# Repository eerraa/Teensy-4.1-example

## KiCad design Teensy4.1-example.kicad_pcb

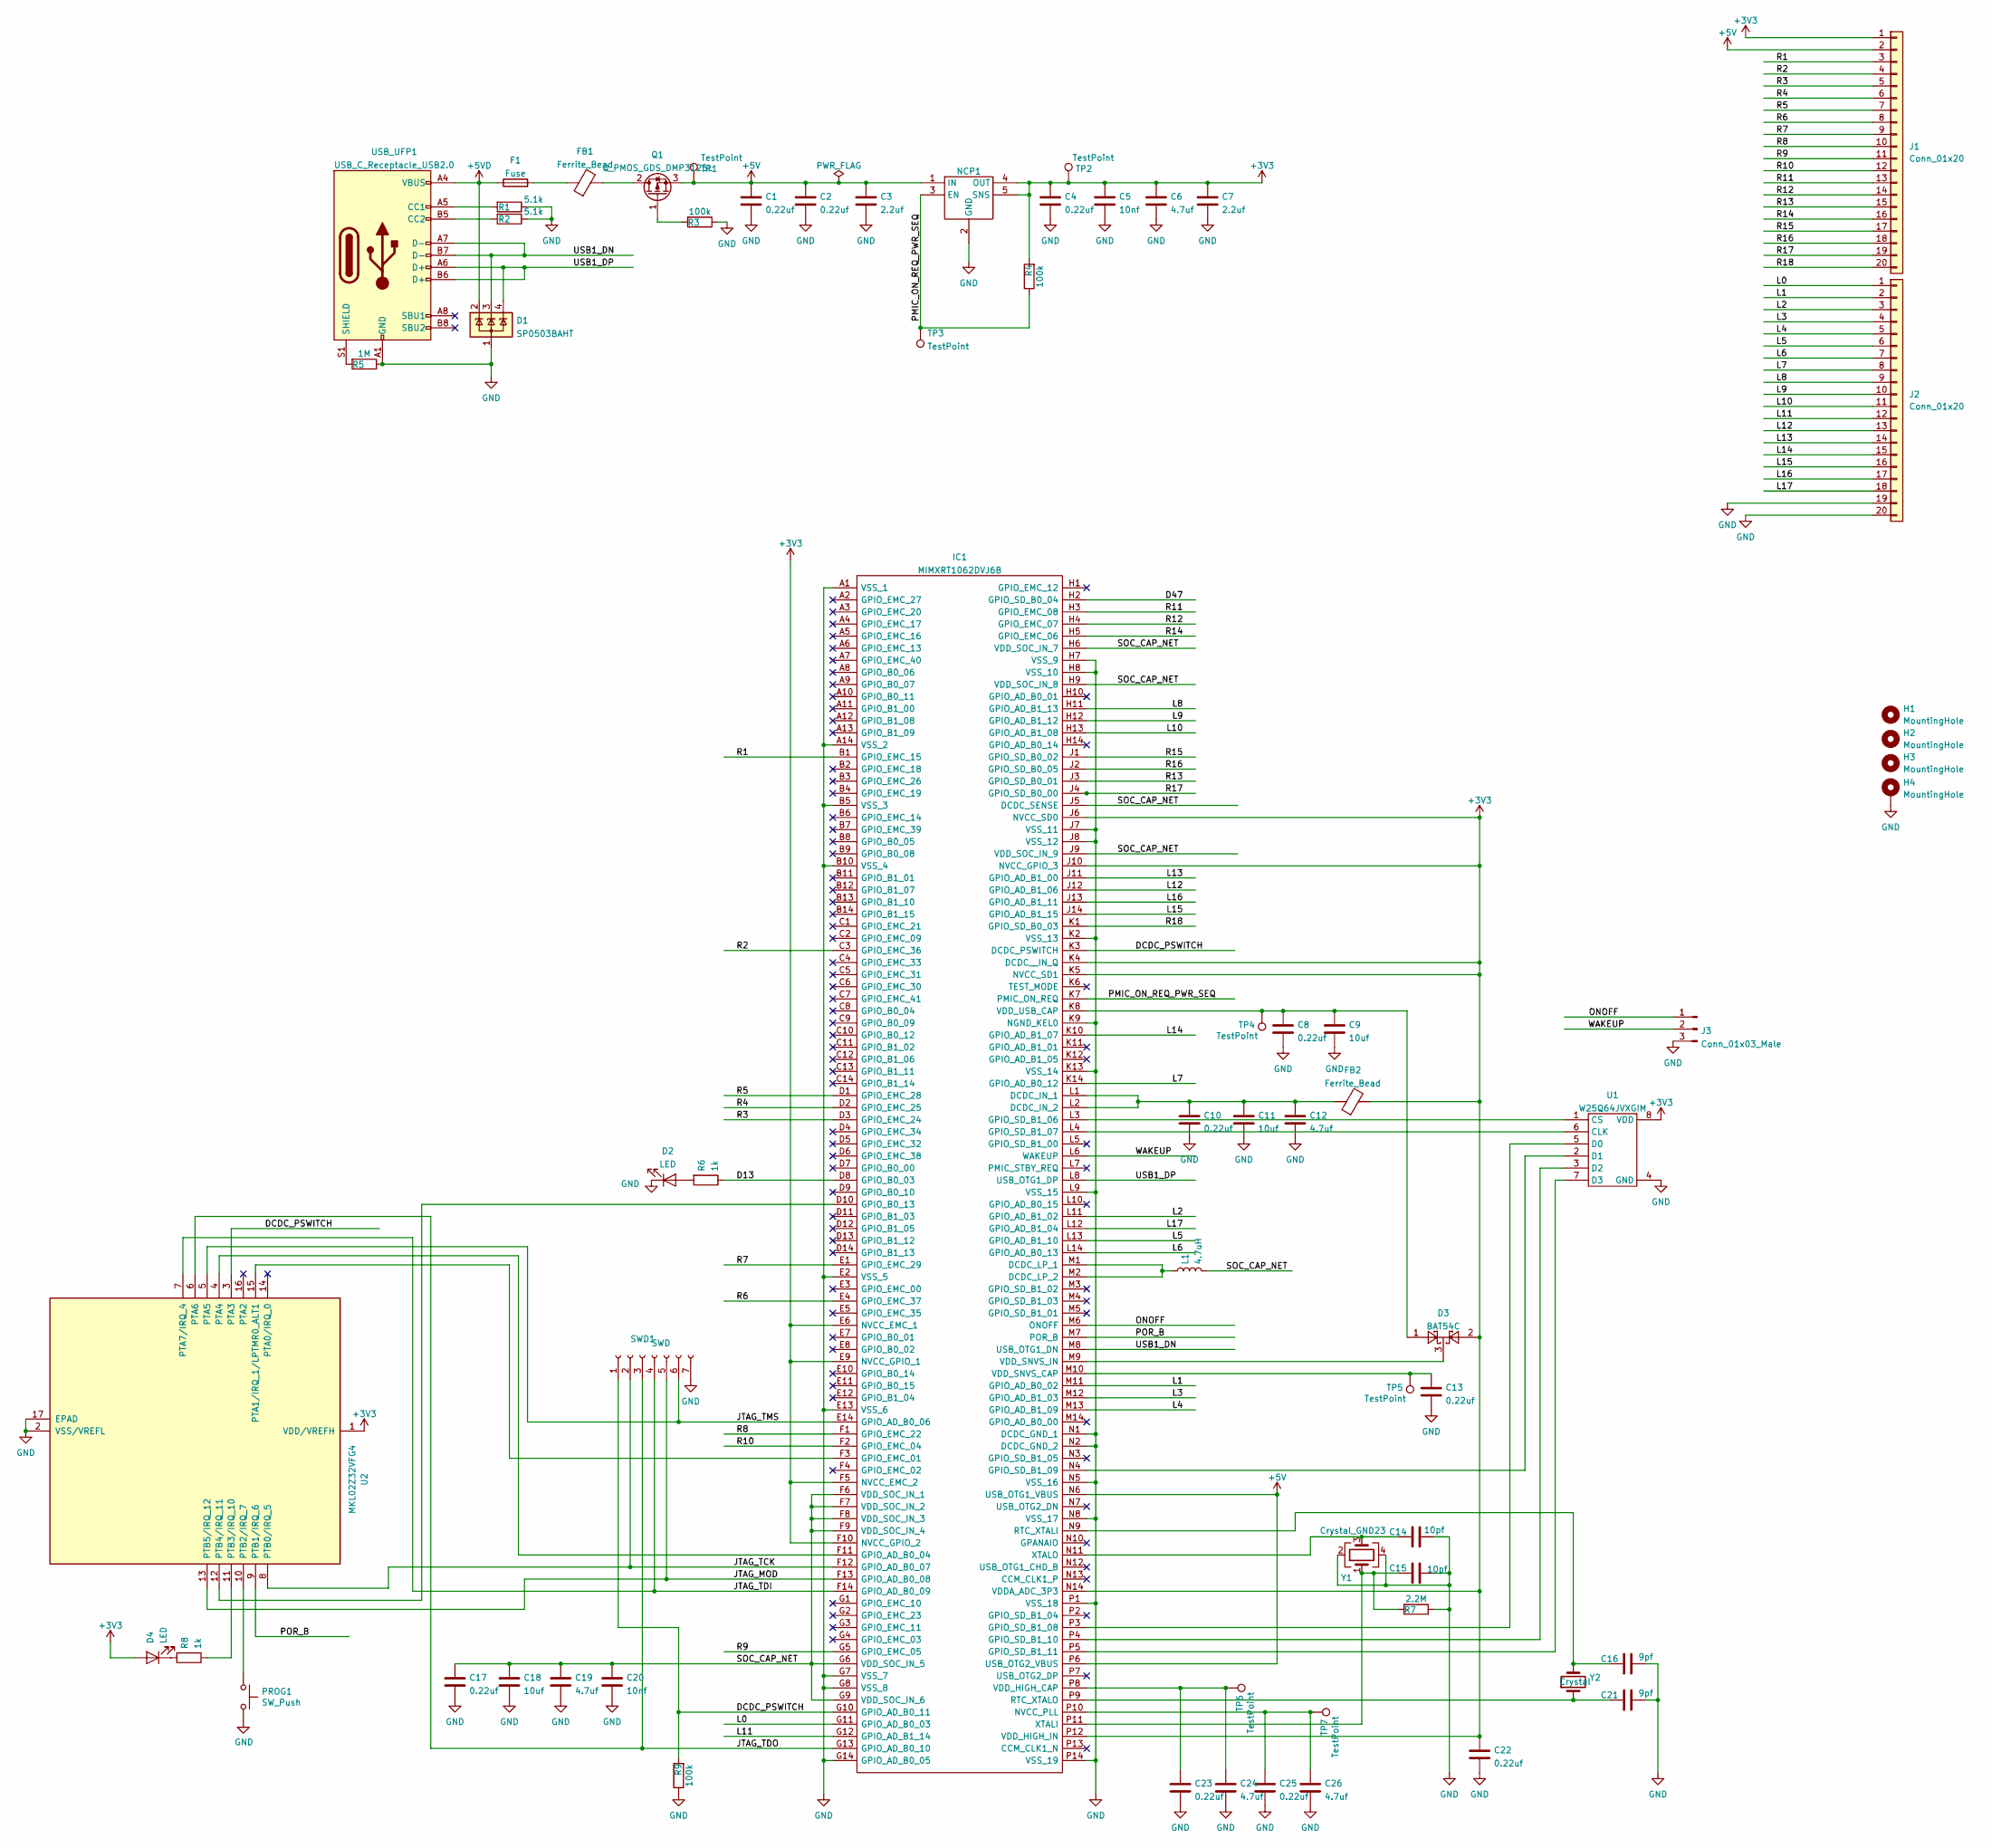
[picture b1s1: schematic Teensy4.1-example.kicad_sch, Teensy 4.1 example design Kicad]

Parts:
C1, C2, C4, C8, C10, C13, C17, C22, C23, C25: 0.22uf; C_0603_1608Metric; MPN CC0603KRX7R6BB224
C3, C7: 2.2uf; C_0603_1608Metric; MPN CL10B225KP8NNNC
C5, C20: 10nf; C_0603_1608Metric; MPN 0603B103K160CT
C6, C12, C19, C24, C26: 4.7uf; C_0603_1608Metric; MPN CL10B475KQ8NQNC
C9, C11, C18: 10uf; C_0805_2012Metric; MPN GRM21BR71A106KA73K
C14, C15: 10pf; C_0603_1608Metric; MPN CC0603KRX7R6BB224
C16, C21: 9pf; C_0603_1608Metric; MPN GRM1885C1H9R0DA01D
D1: SP0503BAHT; SOT-143
D2, D4: LED; LED_0402_1005Metric
D3: BAT54C; SOT-23
F1: Fuse; R_0805_2012Metric; MPN 0ZCK0050FF2E
FB1, FB2: Ferrite_Bead; R_0805_2012Metric; MPN FBMH2012HM121-T‎
H1, H2, H3, H4: MountingHole; MountingHole_2.7mm_M2.5_DIN965_Pad_TopBottom
IC1: MIMXRT1062DVJ6B; BGA196C80P14X14_1200X1200X152; Mouser Part Number 771-MIMXRT1062DVJ6B
J1, J2: Conn_01x20; Hirose_FH12-20S-0.5SH_1x20-1MP_P0.50mm_Horizontal
J3: Conn_01x03_Male; PinHeader_1x03_P2.54mm_Vertical
L1: 4.7uH; C_0805_2012Metric; MPN LQM21PN4R7MGRD
NCP1: OnSemi NCP692, fixed version; DFN-6-1EP_3x3mm_P0.95mm_EP1.7x2.6mm; MPN NCP692MN33T2G
PROG1: SW_Push; KMR241GLFS; MPN KMR241GLFS
Q1: Q_PMOS_GDS_DMP3125L; SOT-23
R1, R2: 5.1k; R_0603_1608Metric; MPN RC0603FR-075K1L
R3, R4, R9: 100k; R_0603_1608Metric
R5: 1M; R_0603_1608Metric
R6, R8: 1k; R_0402_1005Metric
R7: 2.2M; R_0603_1608Metric
SWD1: SWD; PinHeader_1x07_P1.27mm_Vertical
TP1, TP2, TP3, TP4, TP5, TP6, TP7: TestPoint; TestPoint_Pad_D1.0mm
U1: W25Q64JVXGIM; XSON8_4x4mm
U2: MKL02Z32VFG4; QFN-16-1EP_3x3mm_P0.5mm_EP1.8x1.8mm; MPN Custom firmware part
USB_UFP1: USB_C_Receptacle_USB2.0; USB_C_Receptacle_Hroparts_TYPE-C-31-M-12
Y1: Crystal_GND23; Crystal_SMD_Abracon_ABM3B-4Pin_5.0x3.2mm
Y2: Crystal; Crystal_SMD_2012-2Pin_2.0x1.2mm; MPN ABS06-32.768KHZ-9-1-T

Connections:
+3V3: C4.1, C5.1, C6.1, C7.1, C22.1, D3.2, D4.2 (A), FB2.2, IC1.E6 (NVCC_EMC_1), IC1.E9 (NVCC_GPIO_1), IC1.F5 (NVCC_EMC_2), IC1.F10 (NVCC_GPIO_2), IC1.J6 (NVCC_SD0), IC1.J10 (NVCC_GPIO_3), IC1.K4 (DCDC__IN_Q), IC1.K5 (NVCC_SD1), IC1.N14 (VDDA_ADC_3P3), IC1.P12 (VDD_HIGH_IN), J1.1, NCP1.4 (OUT), NCP1.5 (SNS), R4.2, TP2.1, U1.8 (VDD), U2.1 (VDD/VREFH)
+5V: C1.1, C2.1, C3.1, IC1.N6 (USB_OTG1_VBUS), IC1.P6 (USB_OTG2_VBUS), J1.2, NCP1.1 (IN), NCP1.6 (IN), Q1.3 (S), TP1.1
+5VD: D1.2 (K), F1.1, USB_UFP1.A4 (VBUS), USB_UFP1.A9 (VBUS), USB_UFP1.B4 (VBUS), USB_UFP1.B9 (VBUS)
/D13: IC1.D8 (GPIO_B0_03), R6.1
/D47: IC1.H2 (GPIO_SD_B0_04)
/DCDC_PSWITCH: IC1.G10 (GPIO_AD_B0_11), IC1.K3 (DCDC_PSWITCH), R9.2, SWD1.1, U2.3 (PTA3)
/JTAG_MOD: IC1.F13 (GPIO_AD_B0_08), SWD1.5, U2.13 (PTB5/IRQ_12)
/JTAG_TCK: IC1.F12 (GPIO_AD_B0_07), SWD1.2, U2.8 (PTB0/IRQ_5)
/JTAG_TDI: IC1.F14 (GPIO_AD_B0_09), SWD1.4, U2.7 (PTA7/IRQ_4)
/JTAG_TDO: IC1.G13 (GPIO_AD_B0_10), SWD1.3, U2.6 (PTA6)
/JTAG_TMS: IC1.E14 (GPIO_AD_B0_06), SWD1.6, U2.5 (PTA5)
/L0: IC1.G11 (GPIO_AD_B0_03), J2.1
/L1: IC1.M11 (GPIO_AD_B0_02), J2.2
/L2: IC1.L11 (GPIO_AD_B1_02), J2.3
/L3: IC1.M12 (GPIO_AD_B1_03), J2.4
/L4: IC1.M13 (GPIO_AD_B1_09), J2.5
/L5: IC1.L13 (GPIO_AD_B1_10), J2.6
/L6: IC1.L14 (GPIO_AD_B0_13), J2.7
/L7: IC1.K14 (GPIO_AD_B0_12), J2.8
/L8: IC1.H11 (GPIO_AD_B1_13), J2.9
/L9: IC1.H12 (GPIO_AD_B1_12), J2.10
/L10: IC1.H13 (GPIO_AD_B1_08), J2.11
/L11: IC1.G12 (GPIO_AD_B1_14), J2.12
/L12: IC1.J12 (GPIO_AD_B1_06), J2.13
/L13: IC1.J11 (GPIO_AD_B1_00), J2.14
/L14: IC1.K10 (GPIO_AD_B1_07), J2.15
/L15: IC1.J14 (GPIO_AD_B1_15), J2.16
/L16: IC1.J13 (GPIO_AD_B1_11), J2.17
/L17: IC1.L12 (GPIO_AD_B1_04), J2.18
/ONOFF: IC1.M6 (ONOFF), J3.1
/PMIC_ON_REQ_PWR_SEQ: IC1.K7 (PMIC_ON_REQ), NCP1.3 (EN), R4.1, TP3.1
/POR_B: IC1.M7 (POR_B), U2.9 (PTB1/IRQ_6)
/R1: IC1.B1 (GPIO_EMC_15), J1.3
/R2: IC1.C3 (GPIO_EMC_36), J1.4
/R3: IC1.D3 (GPIO_EMC_24), J1.5
/R4: IC1.D2 (GPIO_EMC_25), J1.6
/R5: IC1.D1 (GPIO_EMC_28), J1.7
/R6: IC1.E4 (GPIO_EMC_37), J1.8
/R7: IC1.E1 (GPIO_EMC_29), J1.9
/R8: IC1.F1 (GPIO_EMC_22), J1.10
/R9: IC1.G5 (GPIO_EMC_05), J1.11
/R10: IC1.F2 (GPIO_EMC_04), J1.12
/R11: IC1.H3 (GPIO_EMC_08), J1.13
/R12: IC1.H4 (GPIO_EMC_07), J1.14
/R13: IC1.J3 (GPIO_SD_B0_01), J1.15
/R14: IC1.H5 (GPIO_EMC_06), J1.16
/R15: IC1.J1 (GPIO_SD_B0_02), J1.17
/R16: IC1.J2 (GPIO_SD_B0_05), J1.18
/R17: IC1.J4 (GPIO_SD_B0_00), J1.19
/R18: IC1.K1 (GPIO_SD_B0_03), J1.20
/SOC_CAP_NET: C17.1, C18.1, C19.1, C20.1, IC1.F6 (VDD_SOC_IN_1), IC1.F7 (VDD_SOC_IN_2), IC1.F8 (VDD_SOC_IN_3), IC1.F9 (VDD_SOC_IN_4), IC1.G6 (VDD_SOC_IN_5), IC1.G9 (VDD_SOC_IN_6), IC1.H6 (VDD_SOC_IN_7), IC1.H9 (VDD_SOC_IN_8), IC1.J5 (DCDC_SENSE), IC1.J9 (VDD_SOC_IN_9), L1.2
/USB1_DN: D1.3 (K), IC1.M8 (USB_OTG1_DN), USB_UFP1.A7 (D-), USB_UFP1.B7 (D-)
/USB1_DP: D1.4 (K), IC1.L8 (USB_OTG1_DP), USB_UFP1.A6 (D+), USB_UFP1.B6 (D+)
/WAKEUP: IC1.L6 (WAKEUP), J3.2
GND: C1.2, C2.2, C3.2, C4.2, C5.2, C6.2, C7.2, C8.2, C9.2, C10.2, C11.2, C12.2, C13.2, C14.2, C15.2, C16.2, C17.2, C18.2, C19.2, C20.2, C21.2, C22.2, C23.2, C24.2, C25.2, C26.2, D1.1 (A), D2.1 (K), H4.1, IC1.A1 (VSS_1), IC1.A14 (VSS_2), IC1.B5 (VSS_3), IC1.B10 (VSS_4), IC1.E2 (VSS_5), IC1.E13 (VSS_6), IC1.G7 (VSS_7), IC1.G8 (VSS_8), IC1.G14 (GPIO_AD_B0_05), IC1.H7 (VSS_9), IC1.H8 (VSS_10), IC1.J7 (VSS_11), IC1.J8 (VSS_12), IC1.K2 (VSS_13), IC1.K9 (NGND_KEL0), IC1.K13 (VSS_14), IC1.L9 (VSS_15), IC1.N1 (DCDC_GND_1), IC1.N2 (DCDC_GND_2), IC1.N5 (VSS_16), IC1.N8 (VSS_17), IC1.P1 (VSS_18), IC1.P14 (VSS_19), J2.19, J2.20, J3.3, NCP1.2 (GND), NCP1.7 (GND), PROG1.2, R1.1, R2.1, R3.1, R5.1, R7.1, R9.1, SWD1.7, U1.4 (GND), U2.2 (VSS/VREFL), U2.17 (EPAD), USB_UFP1.A1 (GND), USB_UFP1.A12 (GND), USB_UFP1.B1 (GND), USB_UFP1.B12 (GND), Y1.2, Y1.4
unnamed: D2.2 (A), R6.2
unnamed: D4.1 (K), R8.2
unnamed: F1.2, FB1.1
unnamed: C10.1, C11.1, C12.1, FB2.1, IC1.L1 (DCDC_IN_1), IC1.L2 (DCDC_IN_2)
unnamed: IC1.M1 (DCDC_LP_1), IC1.M2 (DCDC_LP_2), L1.1
unnamed: IC1.F11 (GPIO_AD_B0_04), U2.4 (PTA4)
unnamed: IC1.D10 (GPIO_B0_13), U2.12 (PTB4/IRQ_11)
unnamed: IC1.F3 (GPIO_EMC_01), U2.15 (PTA1/IRQ_1/LPTMR0_ALT1)
unnamed: IC1.L3 (GPIO_SD_B1_06), U1.1 (CS)
unnamed: IC1.L4 (GPIO_SD_B1_07), U1.6 (CLK)
unnamed: IC1.P3 (GPIO_SD_B1_08), U1.5 (D0)
unnamed: IC1.N4 (GPIO_SD_B1_09), U1.2 (D1)
unnamed: IC1.P4 (GPIO_SD_B1_10), U1.3 (D2)
unnamed: IC1.P5 (GPIO_SD_B1_11), U1.7 (D3)
unnamed: C25.1, C26.1, IC1.P10 (NVCC_PLL), TP7.1
unnamed: C16.1, IC1.N9 (RTC_XTALI), Y2.2
unnamed: C21.1, IC1.P9 (RTC_XTALO), Y2.1
unnamed: C23.1, C24.1, IC1.P8 (VDD_HIGH_CAP), TP6.1
unnamed: C13.1, IC1.M10 (VDD_SNVS_CAP), TP5.1
unnamed: D3.3, IC1.M9 (VDD_SNVS_IN)
unnamed: C8.1, C9.1, D3.1, IC1.K8 (VDD_USB_CAP), TP4.1
unnamed: C15.1, IC1.P11 (XTALI), R7.2, Y1.1
unnamed: C14.1, IC1.N11 (XTALO), Y1.3
unnamed: FB1.2, Q1.2 (D)
unnamed: Q1.1 (G), R3.2
unnamed: PROG1.1, U2.10 (PTB2/IRQ_7)
unnamed: R8.1, U2.11 (PTB3/IRQ_10)
unnamed: R1.2, USB_UFP1.A5 (CC1)
unnamed: R2.2, USB_UFP1.B5 (CC2)
unnamed: R5.2, USB_UFP1.S1 (SHIELD)

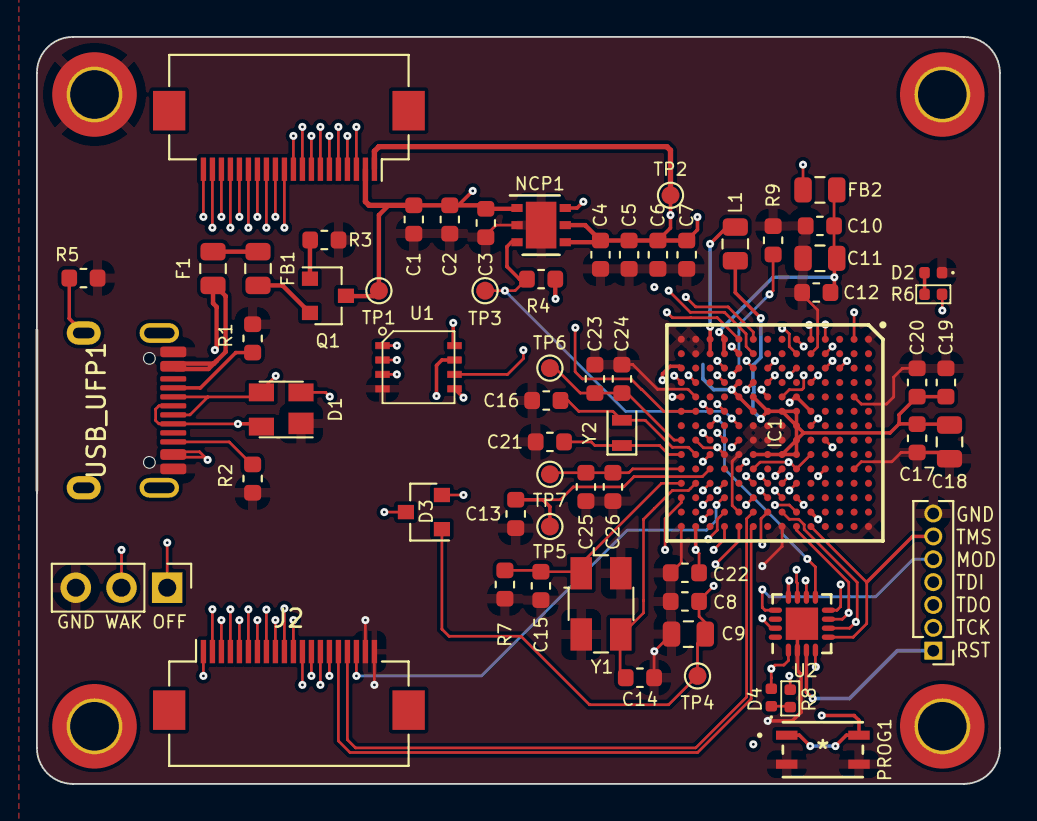
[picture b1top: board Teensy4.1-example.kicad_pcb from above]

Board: 4 copper layers, 53.5 x 41.5 mm, 67 parts (0 on the bottom side), 84 nets.

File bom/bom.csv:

Designator,Footprint,Quantity,Value,LCSC Part #
"C1, C10, C13, C17, C2, C22, C23, C25, C4, C8",603,10,0.22uf,C21120
"C11, C18, C9",805,3,10uf,C15850
"C12, C19, C24, C26, C6",603,5,4.7uf,C19666
"C14, C15",603,2,10pf,C1634
"C16, C21",603,2,9pf,C430713
"C20, C5",603,2,10nf,C57112
"C3, C7",603,2,2.2uf,C23630
D1,SOT-143,1,SP0503BAHT,C7074
"D2, D4",402,2,LED,C20613596
D3,SOT-23,1,BAT54C,C37704
F1,805,1,Fuse,C5220829
"FB1, FB2",805,2,Ferrite_Bead,C454098
IC1,BGA196C80P14X14_1200X1200X152,1,MIMXRT1062DVJ6B,C3216699
"J1, J2",Hirose_FH12-20S-0.5SH_1x20-1MP_P0.50mm_Horizontal,2,Conn_01x20,C596730
J3,PinHeader_1x03_P2.54mm_Vertical,1,Conn_01x03_Male,
L1,805,1,4.7uH,C86090
NCP1,DFN-6-1EP_3x3mm_P0.95mm_EP1.7x2.6mm,1,"OnSemi NCP692, fixed version",C145519
PROG1,KMR241GLFS,1,SW_Push,C221682
Q1,SOT-23,1,Q_PMOS_GDS_DMP3125L,C459542
"R1, R2",603,2,5.1k,C23186
"R3, R4, R9",603,3,100k,C25803
R5,603,1,1M,C22935
"R6, R8",402,2,1k,C11702
R7,603,1,2.2M,C22938
SWD1,PinHeader_1x07_P1.27mm_Vertical,1,SWD,
"TP1, TP2, TP3, TP4, TP5, TP6, TP7",TestPoint_Pad_D1.0mm,7,TestPoint,
U1,XSON8_4x4mm,1,W25Q64JVXGIM,
U2,QFN-16-1EP_3x3mm_P0.5mm_EP1.8x1.8mm,1,MKL02Z32VFG4,
USB_UFP1,USB_C_Receptacle_Hroparts_TYPE-C-31-M-12,1,USB_C_Receptacle_USB2.0,C165948
Y1,Crystal_SMD_Abracon_ABM3B-4Pin_5.0x3.2mm,1,Crystal_GND23,C112587
Y2,Crystal_SMD_2012-2Pin_2.0x1.2mm,1,Crystal,C510776

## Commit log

2024-11-20 Modified

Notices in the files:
parts and their libraries:
Copyright 2016 Accelerated Designs. All rights reserved.
